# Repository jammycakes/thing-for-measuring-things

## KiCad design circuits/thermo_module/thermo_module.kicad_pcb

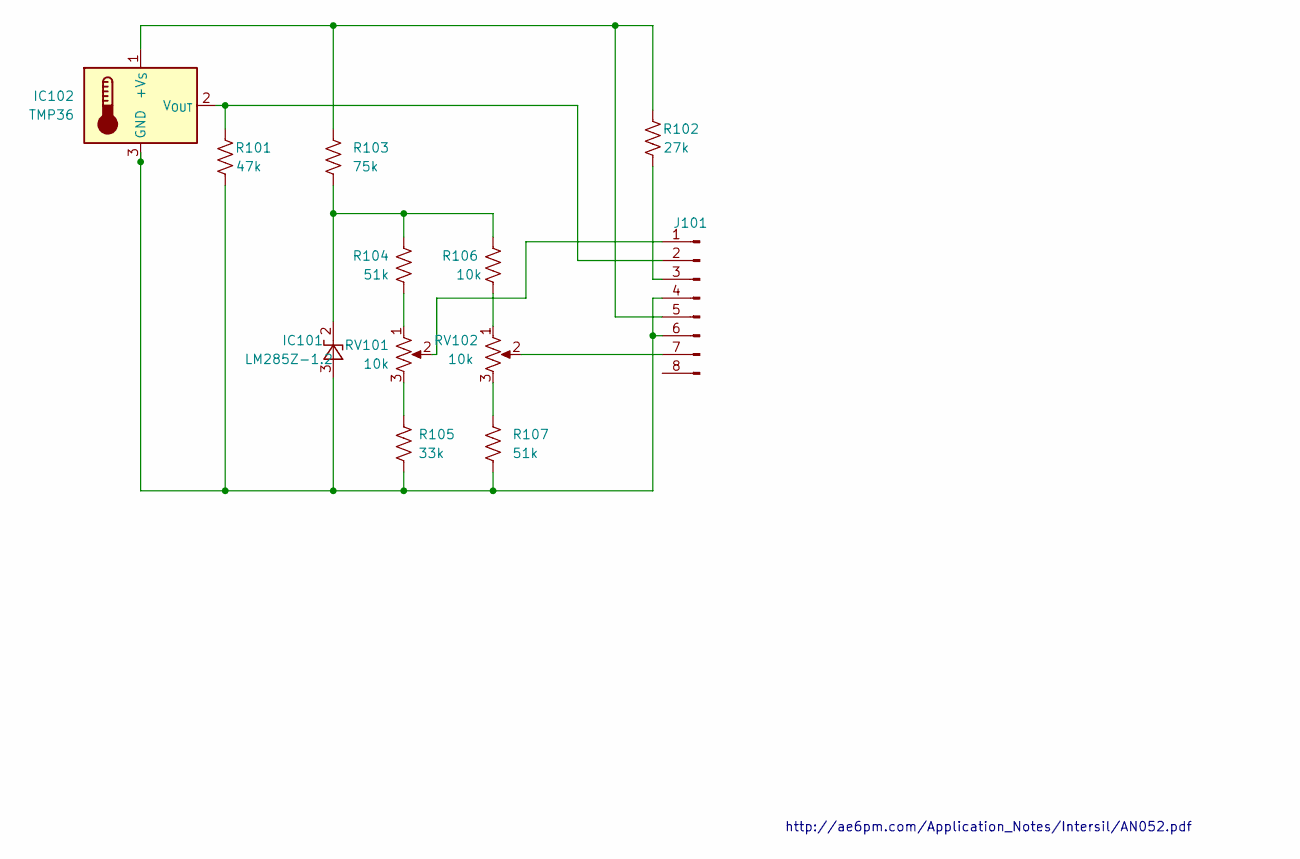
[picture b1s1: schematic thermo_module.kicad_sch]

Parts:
IC101: LM285Z-1.2; TO-92L_Inline_Wide
IC102: TMP36; TO-92L_Inline_Wide
J101: PinHeader_1x08_P2.54mm_Vertical
R101: 47k; R_Axial_DIN0204_L3.6mm_D1.6mm_P7.62mm_Horizontal
R102: 27k; R_Axial_DIN0204_L3.6mm_D1.6mm_P7.62mm_Horizontal
R103: 75k; R_Axial_DIN0204_L3.6mm_D1.6mm_P7.62mm_Horizontal
R104, R107: 51k; R_Axial_DIN0204_L3.6mm_D1.6mm_P7.62mm_Horizontal
R105: 33k; R_Axial_DIN0204_L3.6mm_D1.6mm_P7.62mm_Horizontal
R106: 10k; R_Axial_DIN0204_L3.6mm_D1.6mm_P7.62mm_Horizontal
RV101, RV102: 10k; Potentiometer_Bourns_3266Y_Vertical

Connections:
unnamed: IC101.3 (A), IC102.3 (GND), J101.4, J101.6, R101.1, R105.2, R107.2
unnamed: IC101.2 (K), R103.2, R104.1, R106.1
unnamed: IC102.1 (+V_{S}), J101.5, R102.1, R103.1
unnamed: IC102.2 (V_{OUT}), J101.2, R101.2
unnamed: J101.1, RV101.2
unnamed: J101.3, R102.2
unnamed: J101.7, RV102.2
unnamed: R104.2, RV101.1
unnamed: R105.1, RV101.3
unnamed: R106.2, RV102.1
unnamed: R107.1, RV102.3

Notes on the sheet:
http://ae6pm.com/Application_Notes/Intersil/AN052.pdf

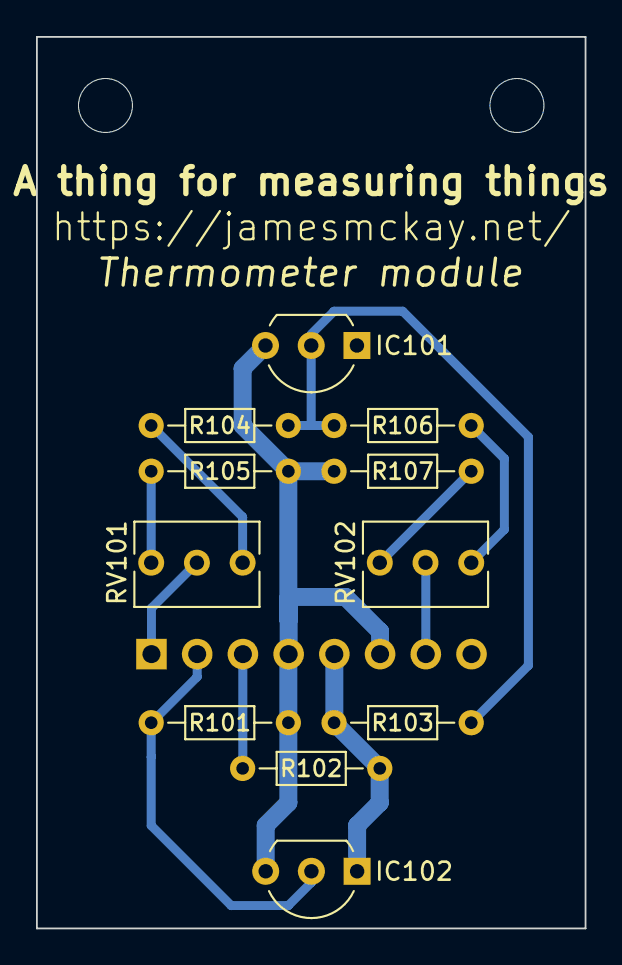
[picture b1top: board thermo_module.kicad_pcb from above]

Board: 2 copper layers, 30.5 x 49.5 mm, 12 parts (1 on the bottom side), 11 nets.

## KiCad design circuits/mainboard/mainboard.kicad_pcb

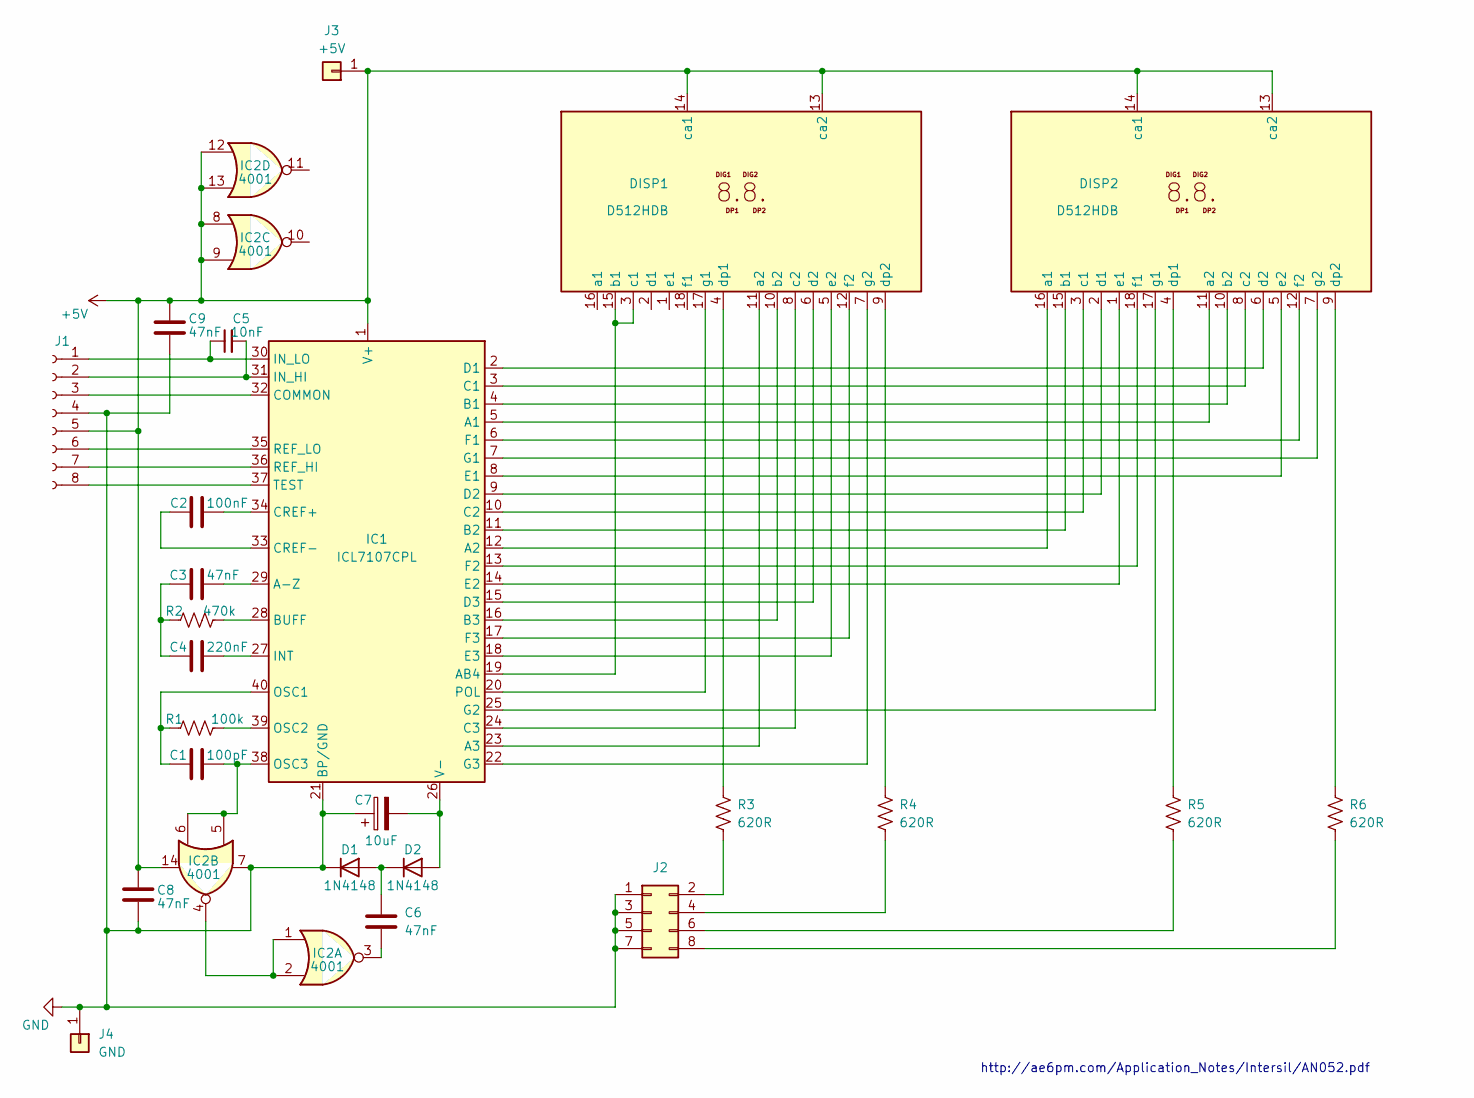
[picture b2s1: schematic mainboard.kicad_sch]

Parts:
C1: 100pF; C_Disc_D4.3mm_W1.9mm_P5.00mm
C2: 100nF; C_Disc_D4.3mm_W1.9mm_P5.00mm
C3, C6, C8, C9: 47nF; C_Disc_D4.3mm_W1.9mm_P5.00mm
C4: 220nF; C_Disc_D4.3mm_W1.9mm_P5.00mm
C5: 10nF; C_Disc_D4.3mm_W1.9mm_P5.00mm
C7: 10uF; CP_Radial_D5.0mm_P2.50mm
D1, D2: 1N4148; D_DO-34_SOD68_P7.62mm_Horizontal
DISP1, DISP2: D512HDB; DA56-11SURKWA
IC1: ICL7107CPL; DIP-40_W15.24mm_Socket_LongPads
IC2: 4001; DIP-14_W7.62mm_LongPads
J1: PinSocket_1x08_P2.54mm_Vertical
J2: PinHeader_2x04_P2.54mm_Vertical
J3: +5V; SolderWire-0.5sqmm_1x01_D0.9mm_OD2.1mm
J4: GND; SolderWire-0.5sqmm_1x01_D0.9mm_OD2.1mm
R1: 100k; R_Axial_DIN0204_L3.6mm_D1.6mm_P7.62mm_Horizontal
R2: 470k; R_Axial_DIN0204_L3.6mm_D1.6mm_P7.62mm_Horizontal
R3, R4, R5, R6: 620R; R_Axial_DIN0204_L3.6mm_D1.6mm_P7.62mm_Horizontal

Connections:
+5V: C8.1, C9.1, DISP1.13 (ca2), DISP1.14 (ca1), DISP2.13 (ca2), DISP2.14 (ca1), IC1.1 (V+), IC2.8, IC2.9, IC2.12, IC2.13, IC2.14, J1.5, J3.1
GND: C7.1, C8.2, C9.2, D1.1 (K), IC1.21 (BP/GND), IC2.7, J1.4, J2.1, J2.3, J2.5, J2.7, J4.1
unnamed: C3.1, C4.1, R2.2
unnamed: C6.2, IC2.3
unnamed: C6.1, D1.2 (A), D2.1 (K)
unnamed: C7.2, D2.2 (A), IC1.26 (V-)
unnamed: DISP1.11 (a2), IC1.23 (A3)
unnamed: DISP1.3 (c1), DISP1.15 (b1), IC1.19 (AB4)
unnamed: DISP1.10 (b2), IC1.16 (B3)
unnamed: DISP1.8 (c2), IC1.24 (C3)
unnamed: DISP1.6 (d2), IC1.15 (D3)
unnamed: DISP1.4 (dp1), R3.2
unnamed: DISP1.9 (dp2), R4.1
unnamed: DISP1.5 (e2), IC1.18 (E3)
unnamed: DISP1.12 (f2), IC1.17 (F3)
unnamed: DISP1.17 (g1), IC1.20 (POL)
unnamed: DISP1.7 (g2), IC1.22 (G3)
unnamed: DISP2.16 (a1), IC1.12 (A2)
unnamed: DISP2.11 (a2), IC1.5 (A1)
unnamed: DISP2.15 (b1), IC1.11 (B2)
unnamed: DISP2.10 (b2), IC1.4 (B1)
unnamed: DISP2.3 (c1), IC1.10 (C2)
unnamed: DISP2.8 (c2), IC1.3 (C1)
unnamed: DISP2.2 (d1), IC1.9 (D2)
unnamed: DISP2.6 (d2), IC1.2 (D1)
unnamed: DISP2.4 (dp1), R5.1
unnamed: DISP2.9 (dp2), R6.1
unnamed: DISP2.1 (e1), IC1.14 (E2)
unnamed: DISP2.5 (e2), IC1.8 (E1)
unnamed: DISP2.18 (f1), IC1.13 (F2)
unnamed: DISP2.12 (f2), IC1.6 (F1)
unnamed: DISP2.17 (g1), IC1.25 (G2)
unnamed: DISP2.7 (g2), IC1.7 (G1)
unnamed: C3.2, IC1.29 (A-Z)
unnamed: IC1.28 (BUFF), R2.1
unnamed: IC1.32 (COMMON), J1.3
unnamed: C2.2, IC1.34 (CREF+)
unnamed: C2.1, IC1.33 (CREF-)
unnamed: C4.2, IC1.27 (INT)
unnamed: C5.2, IC1.31 (IN_HI), J1.2
unnamed: C5.1, IC1.30 (IN_LO), J1.1
unnamed: C1.2, IC1.40 (OSC1), R1.2
unnamed: IC1.39 (OSC2), R1.1
unnamed: C1.1, IC1.38 (OSC3), IC2.5, IC2.6
unnamed: IC1.36 (REF_HI), J1.7
unnamed: IC1.35 (REF_LO), J1.6
unnamed: IC1.37 (TEST), J1.8
unnamed: IC2.1, IC2.2, IC2.4
unnamed: J2.2, R3.1
unnamed: J2.4, R4.2
unnamed: J2.6, R5.2
unnamed: J2.8, R6.2

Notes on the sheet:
http://ae6pm.com/Application_Notes/Intersil/AN052.pdf

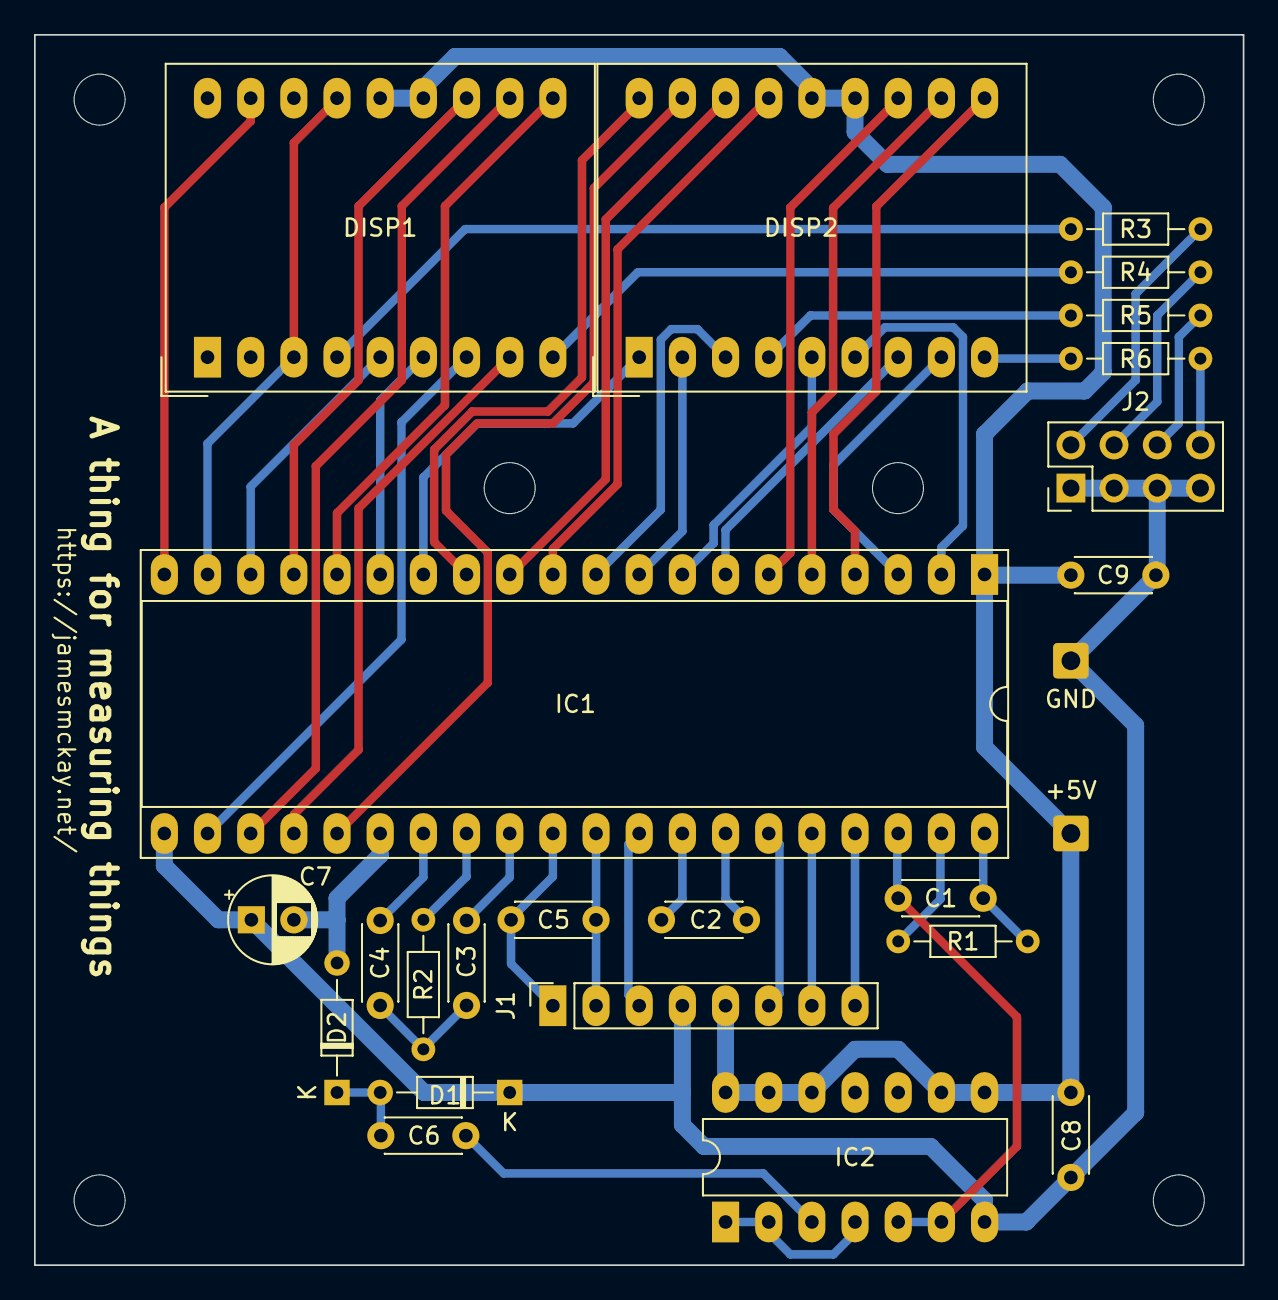
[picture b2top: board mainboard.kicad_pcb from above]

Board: 2 copper layers, 71.1 x 72.4 mm, 25 parts (0 on the bottom side), 52 nets.

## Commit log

2023-11-01 Create a blank KiCad project
2023-11-01 gitignore and reorganise
2023-11-01 Place ICL7107CPL
2023-11-01 Configure oscillator
2023-11-01 Add supporting components and power inverter
2023-11-03 Place all remaining thermometer parts
2023-11-05 Place remaining parts
2023-11-11 Modularise thermometer unit
2023-11-11 Tying up a few loose ends
2023-11-11 Replace display that is no longer available
2023-11-12 PCB for the thermoboard module
2023-11-26 Finish off the PCB
2023-11-26 Separate out the main board
2023-11-30 A bit more tidying up
2023-11-30 Move whole circuit
2023-11-30 Separate out main board into its own project
2023-11-30 Separate out thermo board, and add gerbers
2023-12-28 Redesign thermo module to make it work
2023-12-28 Update gerbers
2024-01-17 Fix for input pins the wrong way round
